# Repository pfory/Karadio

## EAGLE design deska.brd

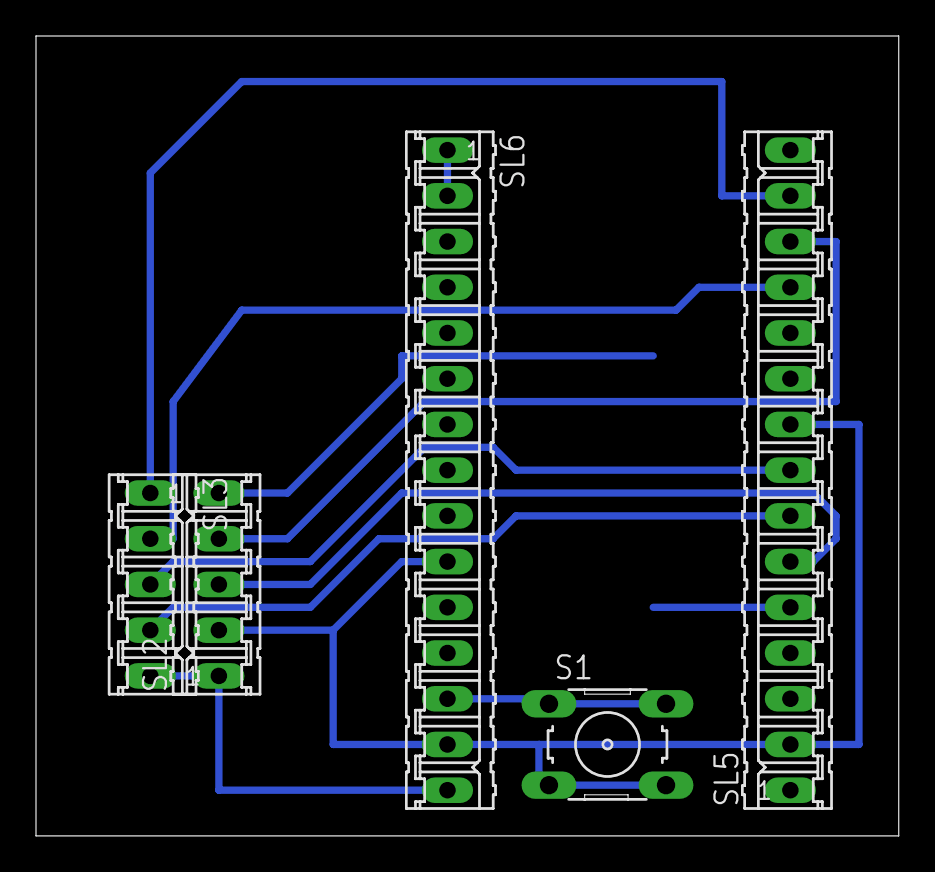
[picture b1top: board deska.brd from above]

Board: 2 copper layers, 47.9 x 44.4 mm, 5 parts (0 on the bottom side), 10 nets.

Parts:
S1: B3F-10XX
SL2, SL3: 05P
SL5, SL6: 15P

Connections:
+5V: SL2.1, SL3.5, SL6.15
GND: S1.3, S1.4, SL2.2, SL5.2, SL5.9, SL6.1, SL6.2, SL6.10, SL6.14
unnamed: SL3.1, SL5.14
unnamed: SL2.5, SL5.5
unnamed: SL3.2, SL5.12
unnamed: SL2.4, SL5.13
unnamed: SL3.3, SL5.8
unnamed: SL2.3, SL5.6
unnamed: SL3.4, SL5.7
unnamed: S1.1, S1.2, SL6.13

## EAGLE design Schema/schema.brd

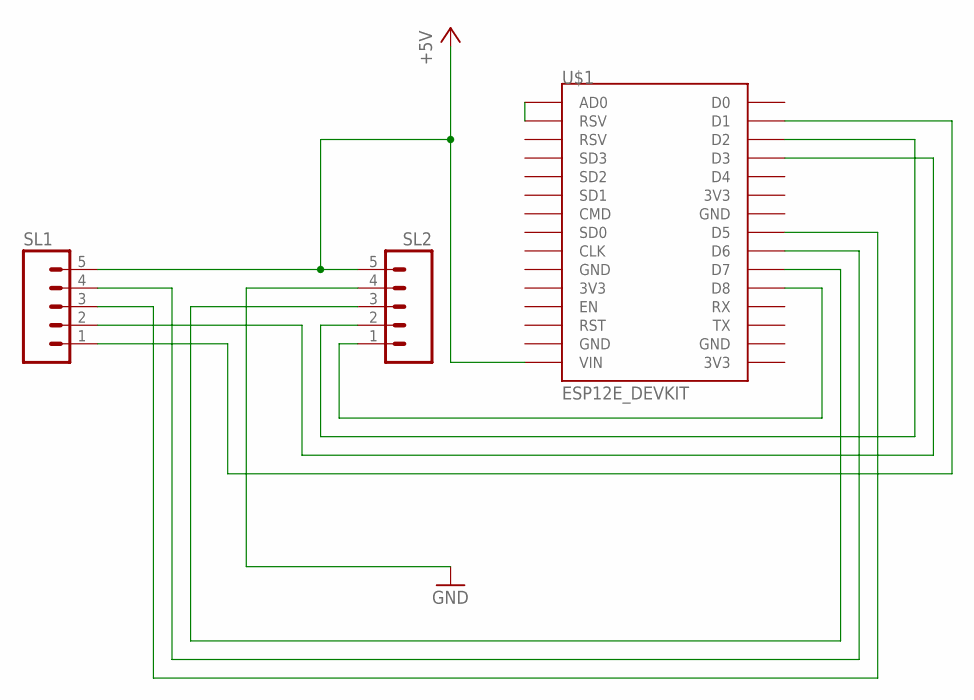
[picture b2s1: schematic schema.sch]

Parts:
SL1, SL2: M05; 05P
U$1: ESP12E_DEVKIT

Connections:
+5V: SL1.5, SL2.5, U$1.VIN
GND: SL2.4
unnamed: U$1.AD0, U$1.RSV@0 (RSV)
unnamed: SL1.4, U$1.D6
unnamed: SL2.3, U$1.D7
unnamed: SL1.3, U$1.D5
unnamed: SL2.2, U$1.D2
unnamed: SL1.2, U$1.D3
unnamed: SL2.1, U$1.D8
unnamed: SL1.1, U$1.D1

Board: 2 copper layers, 3 parts (0 on the bottom side), 9 nets, no tracks yet.

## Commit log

2016-11-15 +schema.brd
2017-03-02 zmena schematu
2017-03-02 odstraneno nadbytecne schema
2017-03-02 upravy desky
2017-03-02 uprava navrhu
